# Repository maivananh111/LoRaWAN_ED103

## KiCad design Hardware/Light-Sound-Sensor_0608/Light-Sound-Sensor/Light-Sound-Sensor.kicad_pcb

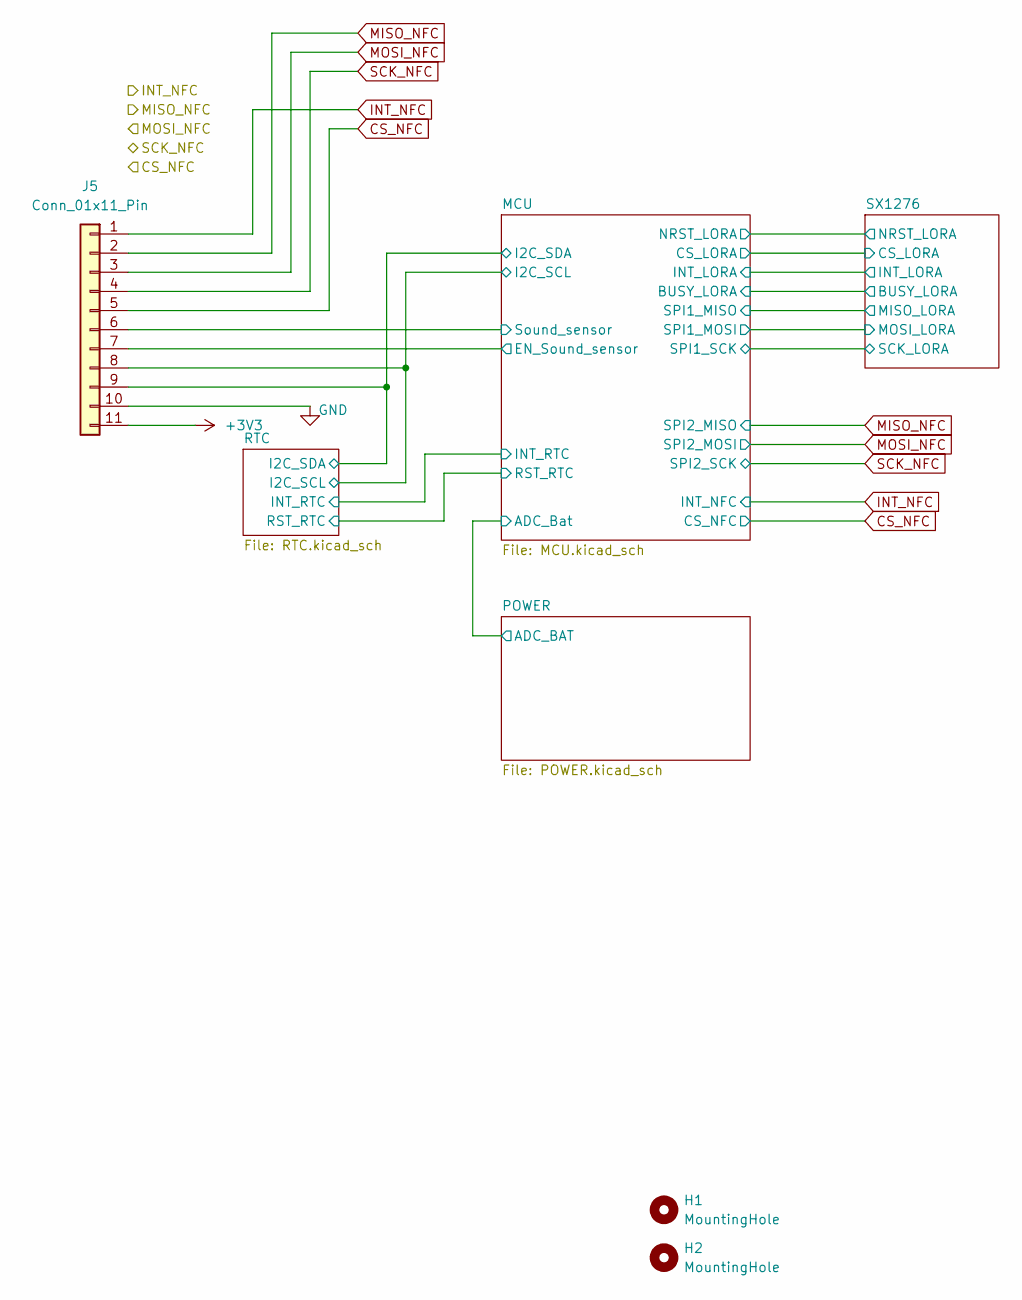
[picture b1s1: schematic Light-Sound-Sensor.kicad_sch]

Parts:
H1, H2: MountingHole; MountingHole_3.2mm_M3_DIN965_Pad
J5: Conn_01x11_Pin; PinHeader_1x11_P2.54mm_Vertical; JLC C5116357

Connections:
+3V3: J5.11; also elsewhere on the board
/MCU/EN_Sound_sensor: J5.7; also elsewhere on the board
/MCU/I2C_SCL: J5.8; also elsewhere on the board
/MCU/I2C_SDA: J5.9; also elsewhere on the board
/MCU/Sound_sensor: J5.6; also elsewhere on the board
CS_NFC: J5.5; also elsewhere on the board
GND: J5.10; also elsewhere on the board
INT_NFC: J5.1; also elsewhere on the board
MISO_NFC: J5.2; also elsewhere on the board
MOSI_NFC: J5.3; also elsewhere on the board
SCK_NFC: J5.4; also elsewhere on the board

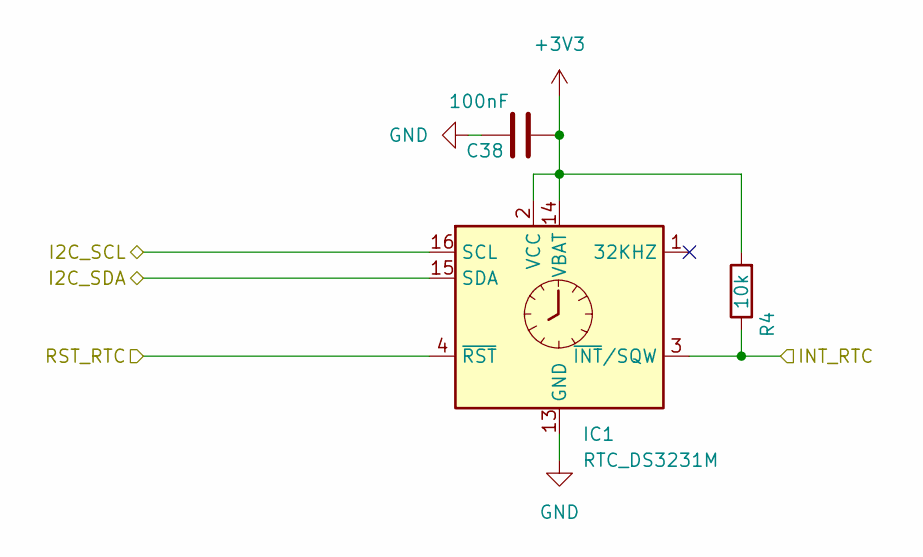
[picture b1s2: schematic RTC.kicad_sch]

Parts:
C38: 100nF; C_0603_1608Metric; JLC C14663
IC1: RTC_DS3231M; SOIC-16W_7.5x10.3mm_P1.27mm; JLC C9866
R4: 10k; R_0603_1608Metric; JLC C25804

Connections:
+3V3: C38.2, IC1.2 (VCC), IC1.14 (VBAT), R4.2; also elsewhere on the board
/MCU/I2C_SCL: IC1.16 (SCL); also elsewhere on the board
/MCU/I2C_SDA: IC1.15 (SDA); also elsewhere on the board
/MCU/INT_RTC: IC1.3 (~INT/SQW), R4.1; also elsewhere on the board
/MCU/RST_RTC: IC1.4 (~RST); also elsewhere on the board
GND: C38.1, IC1.5 (GND), IC1.6 (GND), IC1.7 (GND), IC1.8 (GND), IC1.9 (GND), IC1.10 (GND), IC1.11 (GND), IC1.12 (GND), IC1.13 (GND); also elsewhere on the board

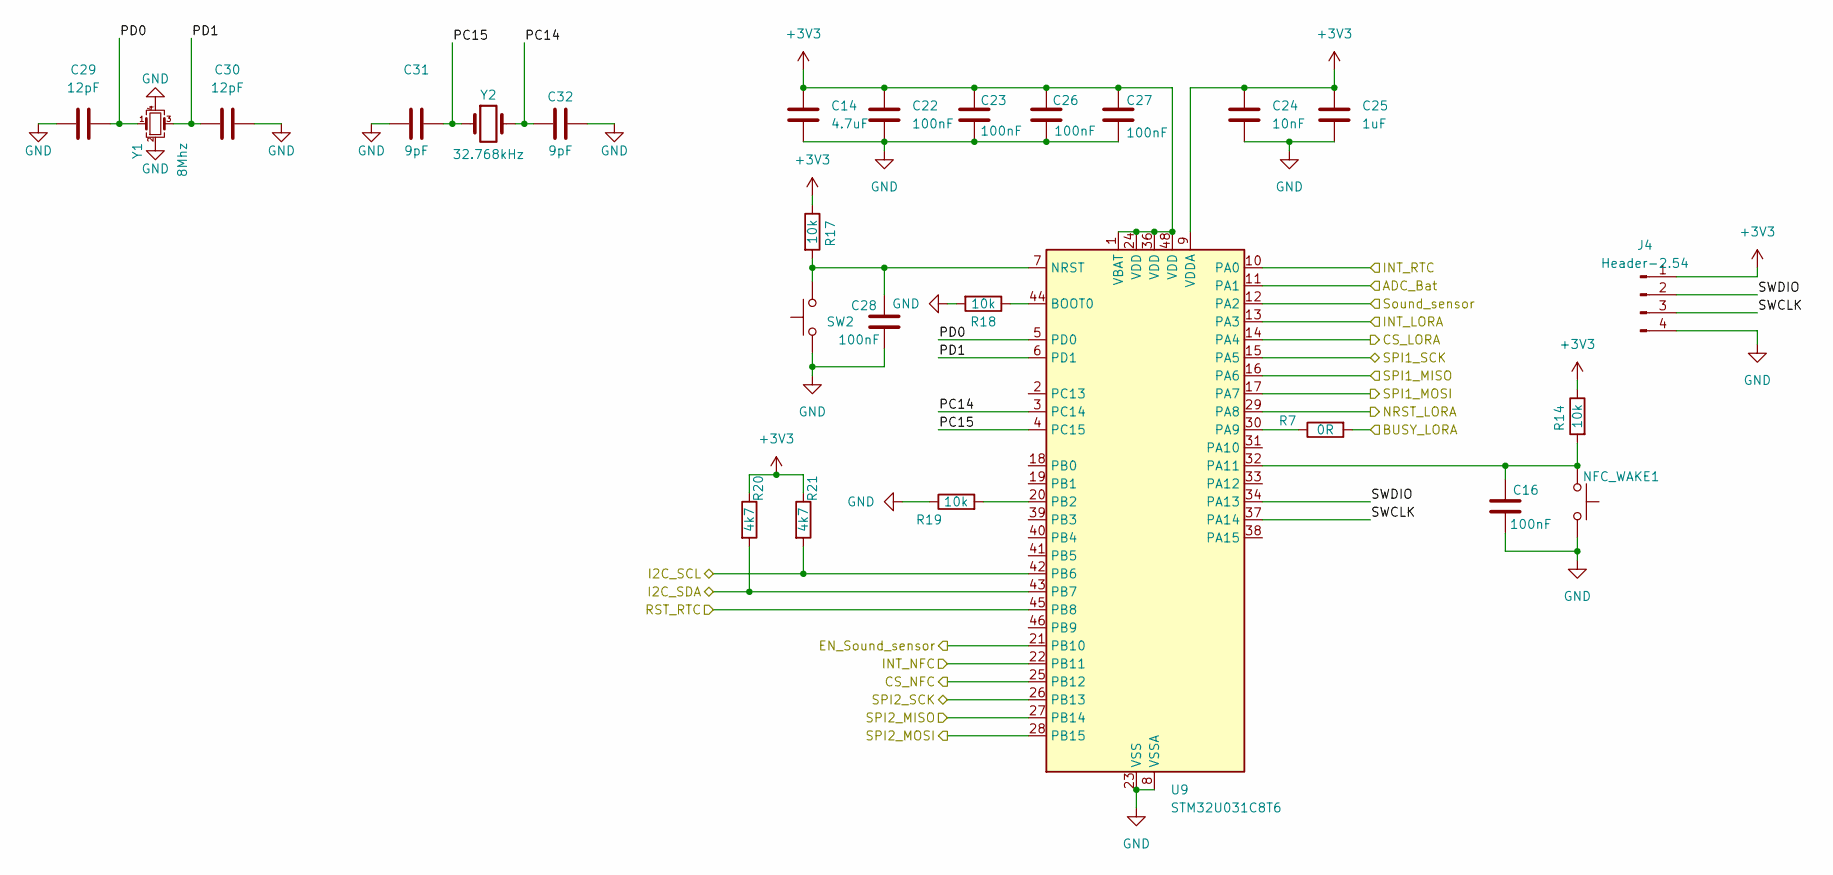
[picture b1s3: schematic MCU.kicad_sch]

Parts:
C14: 4.7uF; C_0603_1608Metric; JLC C76615
C16, C22, C23, C26, C27, C28: 100nF; C_0603_1608Metric; JLC C14663
C24: 10nF; C_0603_1608Metric; JLC C43253
C25: 1uF; C_0603_1608Metric; JLC C126631
C29, C30: 12pF; C_0603_1608Metric; JLC C1642
C31, C32: 9pF; C_0603_1608Metric; JLC C513579
J4: Header-2.54; PinHeader_1x04_P2.54mm_Vertical
NFC_WAKE1: SW_Tactile; SW_SPST_PTS810; JLC C221896
R7: 0R; R_0603_1608Metric; JLC C21189
R14, R17, R18, R19: 10k; R_0603_1608Metric; JLC C25804
R20, R21: 4k7; R_0603_1608Metric; JLC C23162
SW2: SW_Tactile; SW_SPST_PTS810; JLC C221896
U9: STM32U031C8T6; LQFP-48_7x7mm_P0.5mm
Y1: 8Mhz; Crystal_SMD_3225-4Pin_3.2x2.5mm; part C2857622; JLC C400090
Y2: 32.768kHz; Crystal_SMD_3215-2Pin_3.2x1.5mm; Part C2848222; JLC C620155

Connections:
+3V3: C14.1, C22.2, C23.1, C24.1, C25.1, C26.1, C27.1, J4.1, R14.1, R17.1, R20.1, R21.1, U9.1 (VBAT), U9.9 (VDDA), U9.24 (VDD), U9.36 (VDD), U9.48 (VDD); also elsewhere on the board
/MCU/ADC_Bat: U9.11 (PA1); also elsewhere on the board
/MCU/BUSY_LORA: R7.2; also elsewhere on the board
/MCU/CS_LORA: U9.14 (PA4); also elsewhere on the board
/MCU/EN_Sound_sensor: U9.21 (PB10); also elsewhere on the board
/MCU/I2C_SCL: R21.2, U9.42 (PB6); also elsewhere on the board
/MCU/I2C_SDA: R20.2, U9.43 (PB7); also elsewhere on the board
/MCU/INT_LORA: U9.13 (PA3); also elsewhere on the board
/MCU/INT_RTC: U9.10 (PA0); also elsewhere on the board
/MCU/NRST_LORA: U9.29 (PA8); also elsewhere on the board
/MCU/PC14: C32.1, U9.3 (PC14), Y2.2
/MCU/PC15: C31.2, U9.4 (PC15), Y2.1
/MCU/PD0: C29.2, U9.5 (PD0), Y1.1
/MCU/PD1: C30.1, U9.6 (PD1), Y1.3
/MCU/RST_RTC: U9.45 (PB8); also elsewhere on the board
/MCU/SPI1_MISO: U9.16 (PA6); also elsewhere on the board
/MCU/SPI1_MOSI: U9.17 (PA7); also elsewhere on the board
/MCU/SPI1_SCK: U9.15 (PA5); also elsewhere on the board
/MCU/SWCLK: J4.3, U9.37 (PA14)
/MCU/SWDIO: J4.2, U9.34 (PA13)
/MCU/Sound_sensor: U9.12 (PA2); also elsewhere on the board
CS_NFC: U9.25 (PB12); also elsewhere on the board
GND: C14.2, C16.1, C22.1, C23.2, C24.2, C25.2, C26.2, C27.2, C28.1, C29.1, C30.2, C31.1, C32.2, J4.4, NFC_WAKE1.1, R18.2, R19.1, SW2.1, U9.8 (VSSA), U9.23 (VSS), U9.35 (VSS), U9.47 (VSS), Y1.2, Y1.4; also elsewhere on the board
INT_NFC: U9.22 (PB11); also elsewhere on the board
MISO_NFC: U9.27 (PB14); also elsewhere on the board
MOSI_NFC: U9.28 (PB15); also elsewhere on the board
unnamed: R18.1, U9.44 (BOOT0)
unnamed: C28.2, R17.2, SW2.2, U9.7 (NRST)
unnamed: R7.1, U9.30 (PA9)
unnamed: C16.2, NFC_WAKE1.2, R14.2, U9.32 (PA11)
unnamed: R19.2, U9.20 (PB2)
SCK_NFC: U9.26 (PB13); also elsewhere on the board

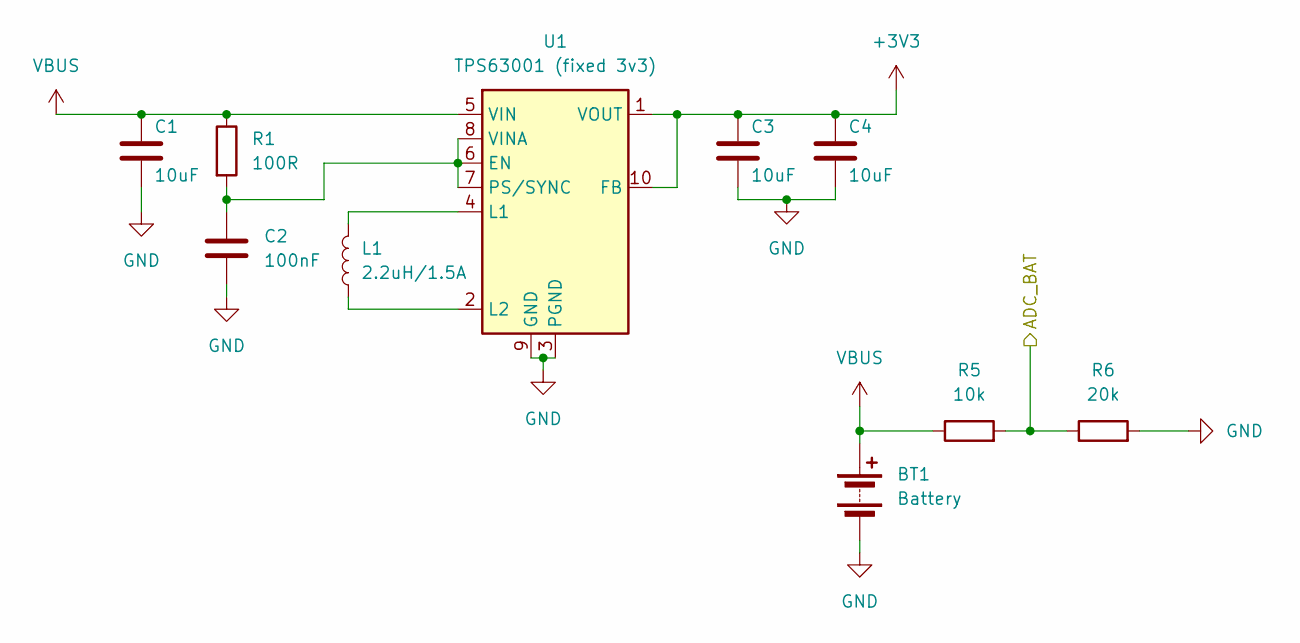
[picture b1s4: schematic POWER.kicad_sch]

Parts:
BT1: Battery; BAT_BC3AAPC
C1: 10uF; C_0603_1608Metric; JLC C91150
C2: 100nF; C_0603_1608Metric; JLC C116838
C3, C4: 10uF; C_0603_1608Metric; JLC C96446
L1: 2.2uH/1.5A; L_0806; Part C439304; JLC C439304
R1: 100R; R_0603_1608Metric; JLC C5123580
R5: 10k; R_0603_1608Metric; JLC C25804
R6: 20k; R_0603_1608Metric; JLC C4184
U1: TPS63001 (fixed 3v3); Texas_DRC0010J_ThermalVias; JLC C28060

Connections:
+3V3: C3.1, C4.1, U1.1 (VOUT), U1.10 (FB); also elsewhere on the board
/MCU/ADC_Bat: R5.2, R6.1; also elsewhere on the board
GND: BT1.2 (-), C1.2, C2.2, C3.2, C4.2, R6.2, U1.3 (PGND), U1.9 (GND), U1.11 (PGND); also elsewhere on the board
unnamed: C2.1, R1.2, U1.6 (EN), U1.7 (PS/SYNC), U1.8 (VINA)
unnamed: L1.2, U1.4 (L1)
unnamed: L1.1, U1.2 (L2)
VBUS: BT1.1 (+), C1.1, R1.1, R5.1, U1.5 (VIN)

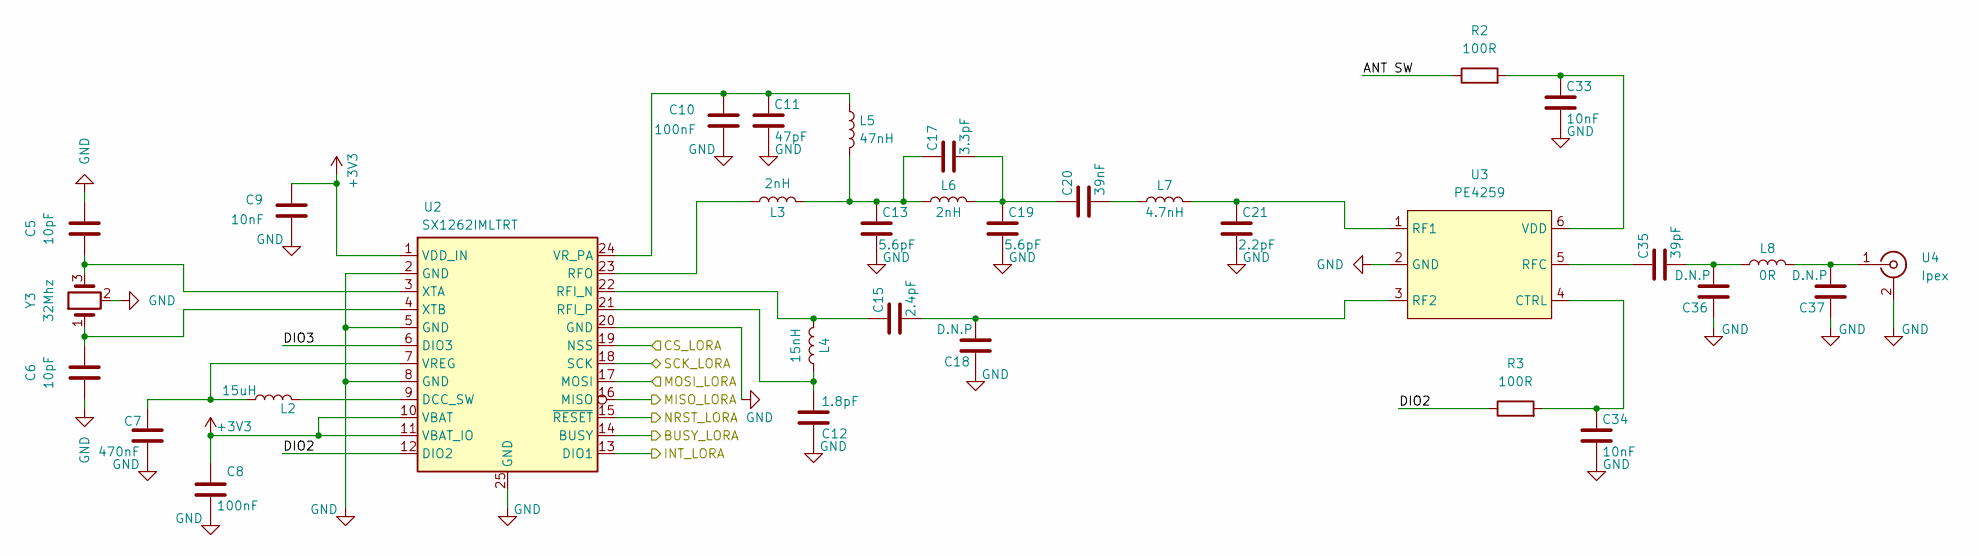
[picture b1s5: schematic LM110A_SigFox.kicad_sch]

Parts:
C5, C6: 10pF; C_0603_1608Metric; JLC C1634
C7: 470nF; C_0603_1608Metric; JLC C77572
C8, C10: 100nF; C_0603_1608Metric; JLC C14663
C9, C33, C34: 10nF; C_0603_1608Metric; JLC C43253
C11: 47pF; C_0603_1608Metric; JLC C105622
C12: 1.8pF; C_0603_1608Metric; JLC C1640
C13, C19: 5.6pF; C_0603_1608Metric; JLC C1674
C15: 2.4pF; C_0603_1608Metric; JLC C27741
C17: 3.3pF; C_0603_1608Metric; JLC C1660
C18, C36, C37: D.N.P; C_0603_1608Metric
C20: 39nF; C_0603_1608Metric; JLC C107091
C21: 2.2pF; C_0603_1608Metric; JLC C1651
C35: 39pF; C_0603_1608Metric; JLC C107049
L2: 15uH; L_0603_1608Metric; JLC C57838
L3, L6: 2nH; L_0603_1608Metric; JLC C370234
L4: 15nH; L_0603_1608Metric; JLC C23651
L5: 47nH; L_0603_1608Metric; JLC C29683
L7: 4.7nH; L_0603_1608Metric; JLC C1030
L8: 0R; L_0603_1608Metric; JLC C21189
R2, R3: 100R; R_0603_1608Metric; JLC C22775
U2: SX1262IMLTRT; QFN-24-1EP_4x4mm_P0.5mm_EP2.6x2.6mm
U3: PE4259; SOT-363_SC-70-6; JLC C470892
U4: Ipex; Conn_IPEX_ANT; JLC C496552
Y3: 32Mhz; Crystal_SMD_3225-4Pin_3.2x2.5mm; JLC C9009

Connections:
+3V3: C8.1, C9.1, U2.1 (VDD_IN), U2.10 (VBAT), U2.11 (VBAT_IO); also elsewhere on the board
/MCU/BUSY_LORA: U2.14 (BUSY); also elsewhere on the board
/MCU/CS_LORA: U2.19 (NSS); also elsewhere on the board
/MCU/INT_LORA: U2.13 (DIO1); also elsewhere on the board
/MCU/NRST_LORA: U2.15 (~RESET); also elsewhere on the board
/MCU/SPI1_MISO: U2.16 (MISO); also elsewhere on the board
/MCU/SPI1_MOSI: U2.17 (MOSI); also elsewhere on the board
/MCU/SPI1_SCK: U2.18 (SCK); also elsewhere on the board
/SX1276/ANT SW: R2.1
/SX1276/DIO2: R3.1, U2.12 (DIO2)
/SX1276/DIO3: U2.6 (DIO3)
GND: C5.2, C6.1, C7.2, C8.2, C9.2, C10.2, C11.2, C12.1, C13.2, C18.1, C19.2, C21.2, C33.2, C34.2, C36.1, C37.1, U2.2 (GND), U2.5 (GND), U2.8 (GND), U2.20 (GND), U2.25 (GND), U3.2 (GND), U4.2, U4.3, Y3.2, Y3.4; also elsewhere on the board
unnamed: C13.1, C17.1, L3.2, L5.2, L6.1
unnamed: C17.2, C19.1, C20.1, L6.2
unnamed: C20.2, L7.1
unnamed: C35.2, C36.2, L8.1
unnamed: C37.2, L8.2, U4.1
unnamed: L2.2, U2.9 (DCC_SW)
unnamed: C15.1, L4.2, U2.22 (RFI_N)
unnamed: C12.2, L4.1, U2.21 (RFI_P)
unnamed: L3.1, U2.23 (RFO)
unnamed: C7.1, L2.1, U2.7 (VREG)
unnamed: C10.1, C11.1, L5.1, U2.24 (VR_PA)
unnamed: C5.1, U2.3 (XTA), Y3.3
unnamed: C6.2, U2.4 (XTB), Y3.1
unnamed: C34.1, R3.2, U3.4 (CTRL)
unnamed: C21.1, L7.2, U3.1 (RF1)
unnamed: C15.2, C18.2, U3.3 (RF2)
unnamed: C35.1, U3.5 (RFC)
unnamed: C33.1, R2.2, U3.6 (VDD)

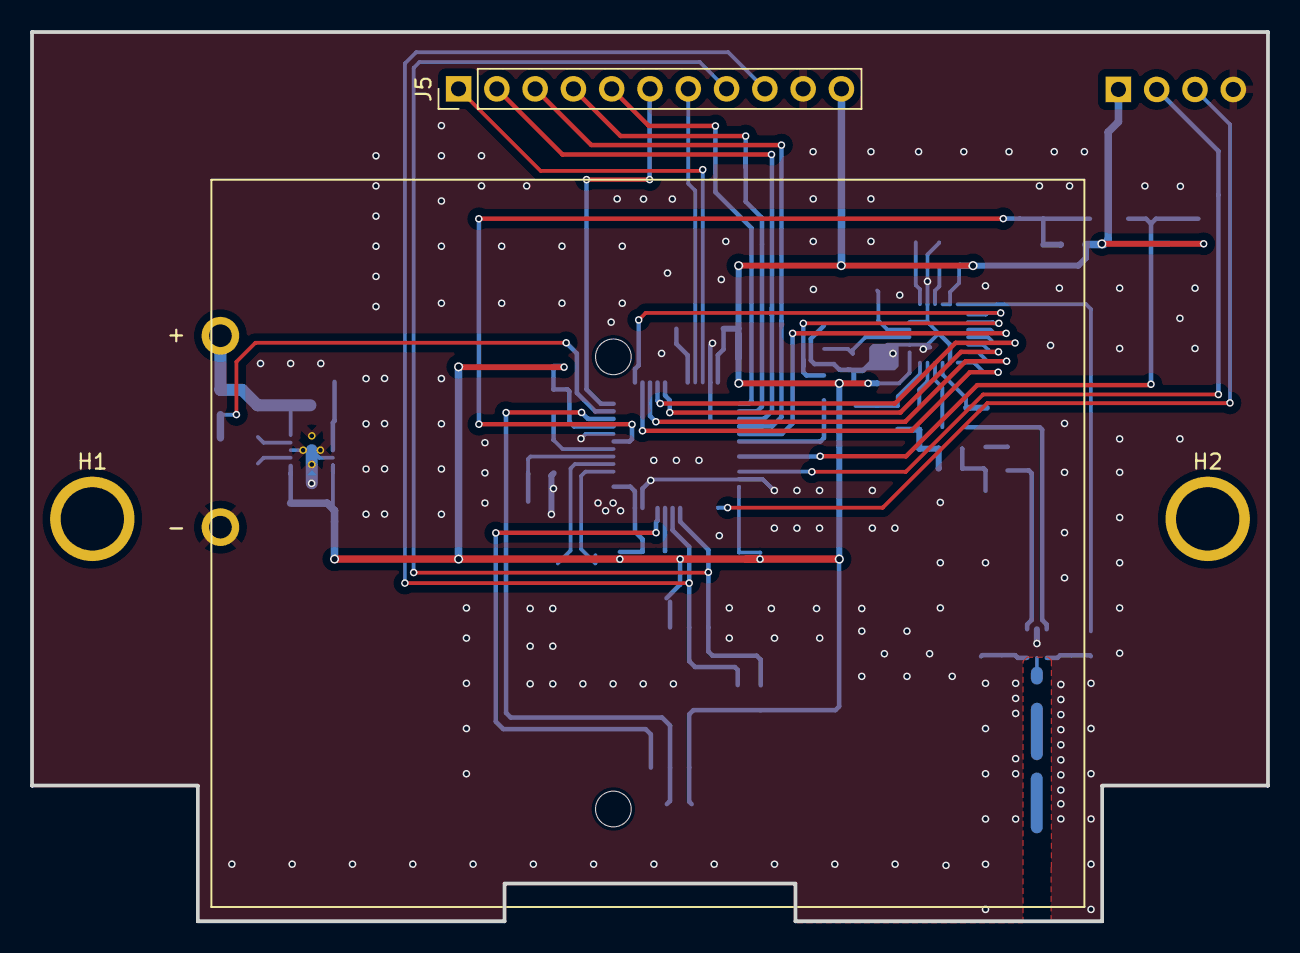
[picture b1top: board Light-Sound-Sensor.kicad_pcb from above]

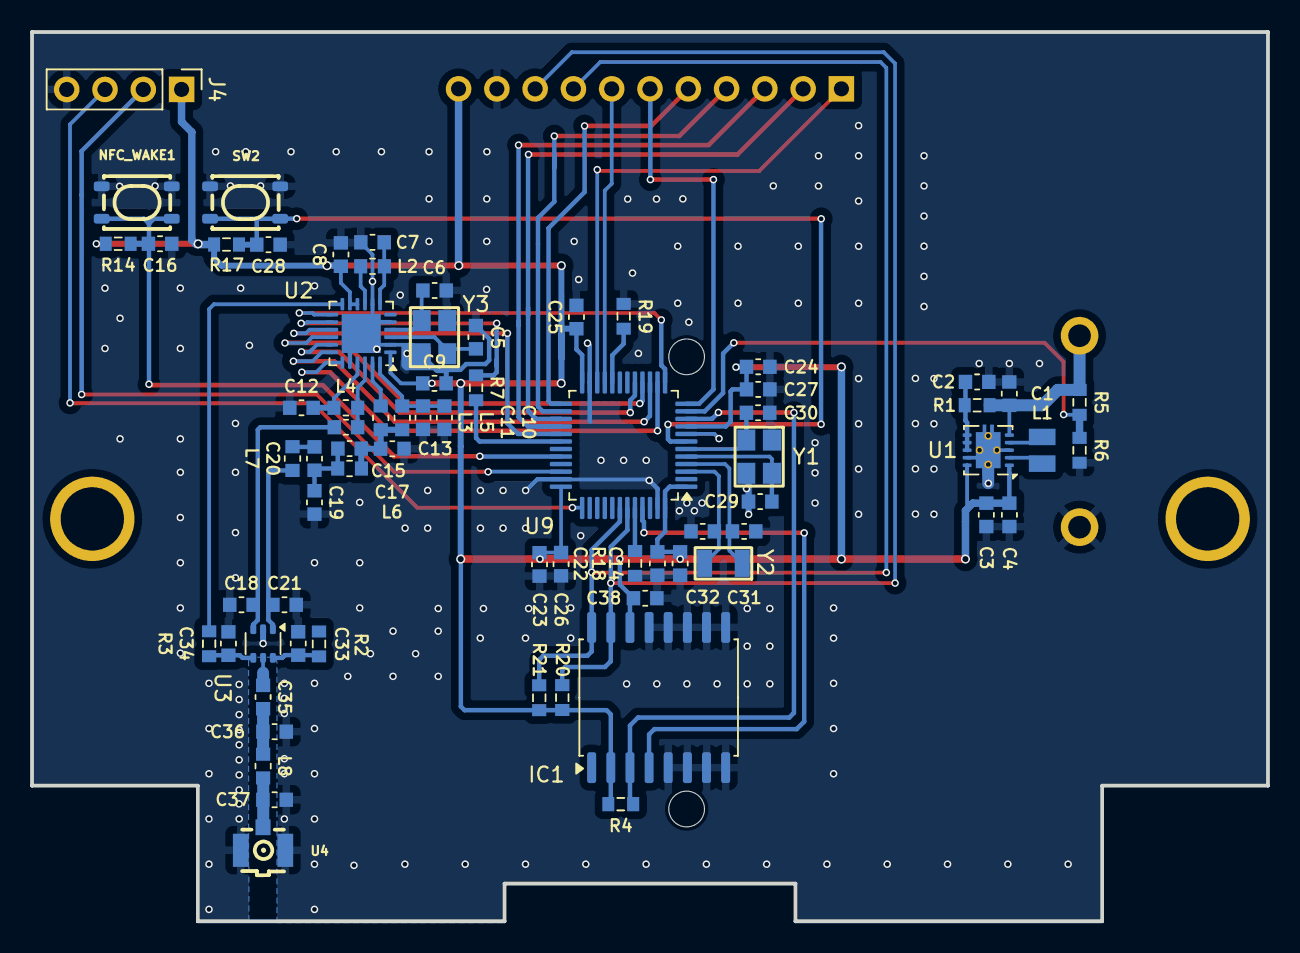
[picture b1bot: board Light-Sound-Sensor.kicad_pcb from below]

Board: 2 copper layers, 82.0 x 59.0 mm, 75 parts (71 on the bottom side), 55 nets.

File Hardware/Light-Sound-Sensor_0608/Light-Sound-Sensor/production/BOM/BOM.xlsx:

Designator | Footprint | Quantity | Value | LCSC Part # | Digikey
BT1 | BAT_BC3AAPC | 1 | Battery |  | BC3AAPC-ND
C1, C3, C4 | 603 | 3 | 10uF | C96446
C10, C16, C2, C22, C23, C26, C27, C28, C38, C8 | 603 | 10 | 100nF | C14663
C11 | 603 | 1 | 47pF | C105622
C12 | 603 | 1 | 1.8pF | C1640
C13, C19 | 603 | 2 | 5.6pF | C1674
C14 | 603 | 1 | 4.7uF | C76615
C15 | 603 | 1 | 2.4pF | C27741
C17 | 603 | 1 | 3.3pF | C1660
C20 | 603 | 1 | 39nF | C107091
C21 | 603 | 1 | 2.2pF | C1651
C24, C33, C34, C9 | 603 | 4 | 10nF | C43253
C25 | 603 | 1 | 1uF | C126631
C29, C30 | 603 | 2 | 12pF | C1642
C31, C32 | 603 | 2 | 9pF | C513579
C35 | 603 | 1 | 39pF | C107049
C5, C6 | 603 | 2 | 10pF | C1634
C7 | 603 | 1 | 470nF | C77572
IC1 | SOIC-16W_7.5x10.3mm_P1.27mm | 1 | RTC_DS3231M | NPN
J5 | PinHeader_1x11_P2.54mm_Vertical | 1 | Conn_01x11_Pin | C5116357
L1 | L_0806 | 1 | 2.2uH/1.5A | C439304
L2 | 603 | 1 | 15uH | C57838
L3, L6 | 603 | 2 | 2nH | C370234
L4 | 603 | 1 | 15nH | C23651
L5 | 603 | 1 | 47nH | C29683
L7 | 603 | 1 | 4.7nH | C1030
L8, R7 | 603 | 2 | 0R | C21189
NFC_WAKE1, SW2 | SW_SPST_PTS810 | 2 | SW_Tactile | C221896
R1, R2, R3 | 603 | 3 | 100R | C22775
R14, R17, R18, R19, R4, R5 | 603 | 6 | 10k | C25804
R20, R21 | 603 | 2 | 4k7 | C23162
R6 | 603 | 1 | 20k | C4184
U1 | Texas_DRC0010J_ThermalVias | 1 | TPS63001 (fixed 3v3) | C28060
U2 | QFN-24-1EP_4x4mm_P0.5mm_EP2.6x2.6mm | 1 | SX1262IMLTRT | C191341
U3 | SOT-363_SC-70-6 | 1 | PE4259 | C470892
U4 | Conn_IPEX_ANT | 1 | Ipex | C496552
U9 | LQFP-48_7x7mm_P0.5mm | 1 | STM32U031C8T6 |  | 497-STM32U031C8T6-ND
Y1 | Crystal_SMD_3225-4Pin_3.2x2.5mm | 1 | 8Mhz | C400090
Y2 | Crystal_SMD_3215-2Pin_3.2x1.5mm | 1 | 32.768kHz | C620155
Y3 | Crystal_SMD_3225-4Pin_3.2x2.5mm | 1 | 32Mhz | C9009

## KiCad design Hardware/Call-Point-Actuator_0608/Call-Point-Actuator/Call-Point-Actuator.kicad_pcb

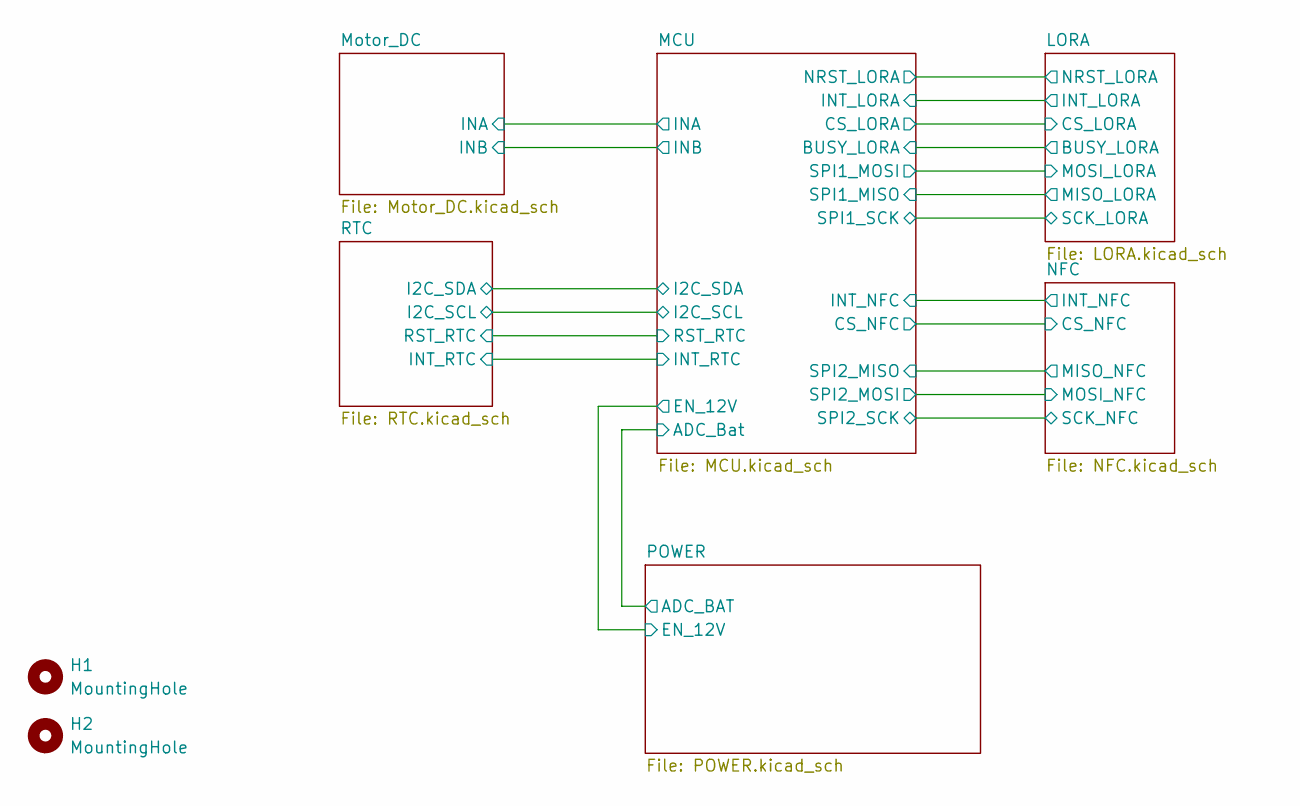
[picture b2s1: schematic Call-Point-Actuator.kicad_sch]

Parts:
H1, H2: MountingHole; MountingHole_3.2mm_M3_DIN965_Pad

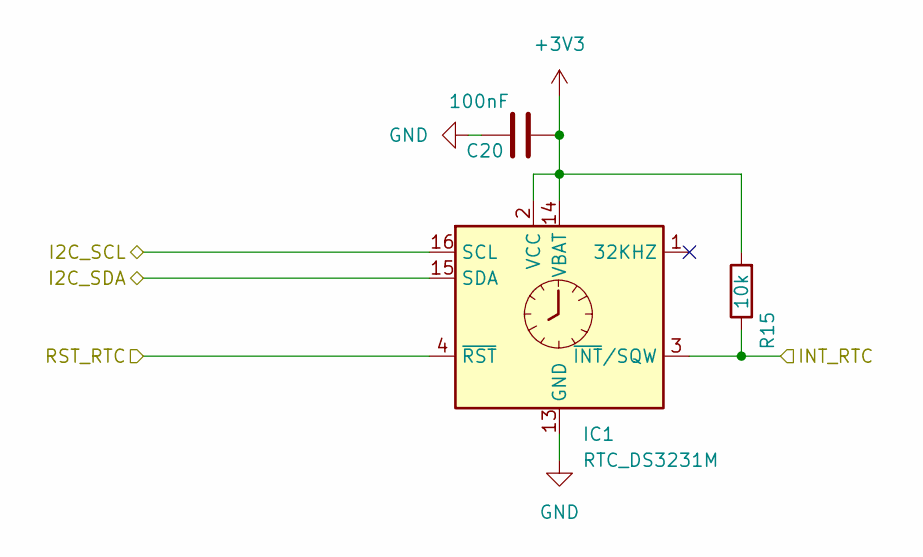
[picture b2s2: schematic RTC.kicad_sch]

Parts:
C20: 100nF; C_0603_1608Metric; JLC C14663
IC1: RTC_DS3231M; SOIC-16W_7.5x10.3mm_P1.27mm; JLC C9866
R15: 10k; R_0603_1608Metric; JLC C25804

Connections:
+3V3: C20.2, IC1.2 (VCC), IC1.14 (VBAT), R15.2; also elsewhere on the board
/MCU/I2C_SCL: IC1.16 (SCL); also elsewhere on the board
/MCU/I2C_SDA: IC1.15 (SDA); also elsewhere on the board
/MCU/INT_RTC: IC1.3 (~INT/SQW), R15.1; also elsewhere on the board
/MCU/RST_RTC: IC1.4 (~RST); also elsewhere on the board
GND: C20.1, IC1.5 (GND), IC1.6 (GND), IC1.7 (GND), IC1.8 (GND), IC1.9 (GND), IC1.10 (GND), IC1.11 (GND), IC1.12 (GND), IC1.13 (GND); also elsewhere on the board

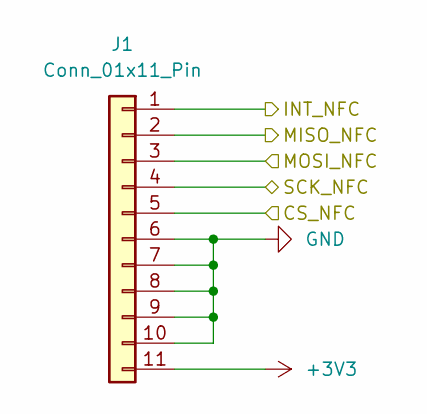
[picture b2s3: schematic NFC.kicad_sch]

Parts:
J1: Conn_01x11_Pin; PinHeader_1x11_P2.54mm_Vertical; JLC C5116357

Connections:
+3V3: J1.11; also elsewhere on the board
/MCU/CS_NFC: J1.5; also elsewhere on the board
/MCU/INT_NFC: J1.1; also elsewhere on the board
/MCU/SPI2_MISO: J1.2; also elsewhere on the board
/MCU/SPI2_MOSI: J1.3; also elsewhere on the board
/MCU/SPI2_SCK: J1.4; also elsewhere on the board
GND: J1.6, J1.7, J1.8, J1.9, J1.10; also elsewhere on the board

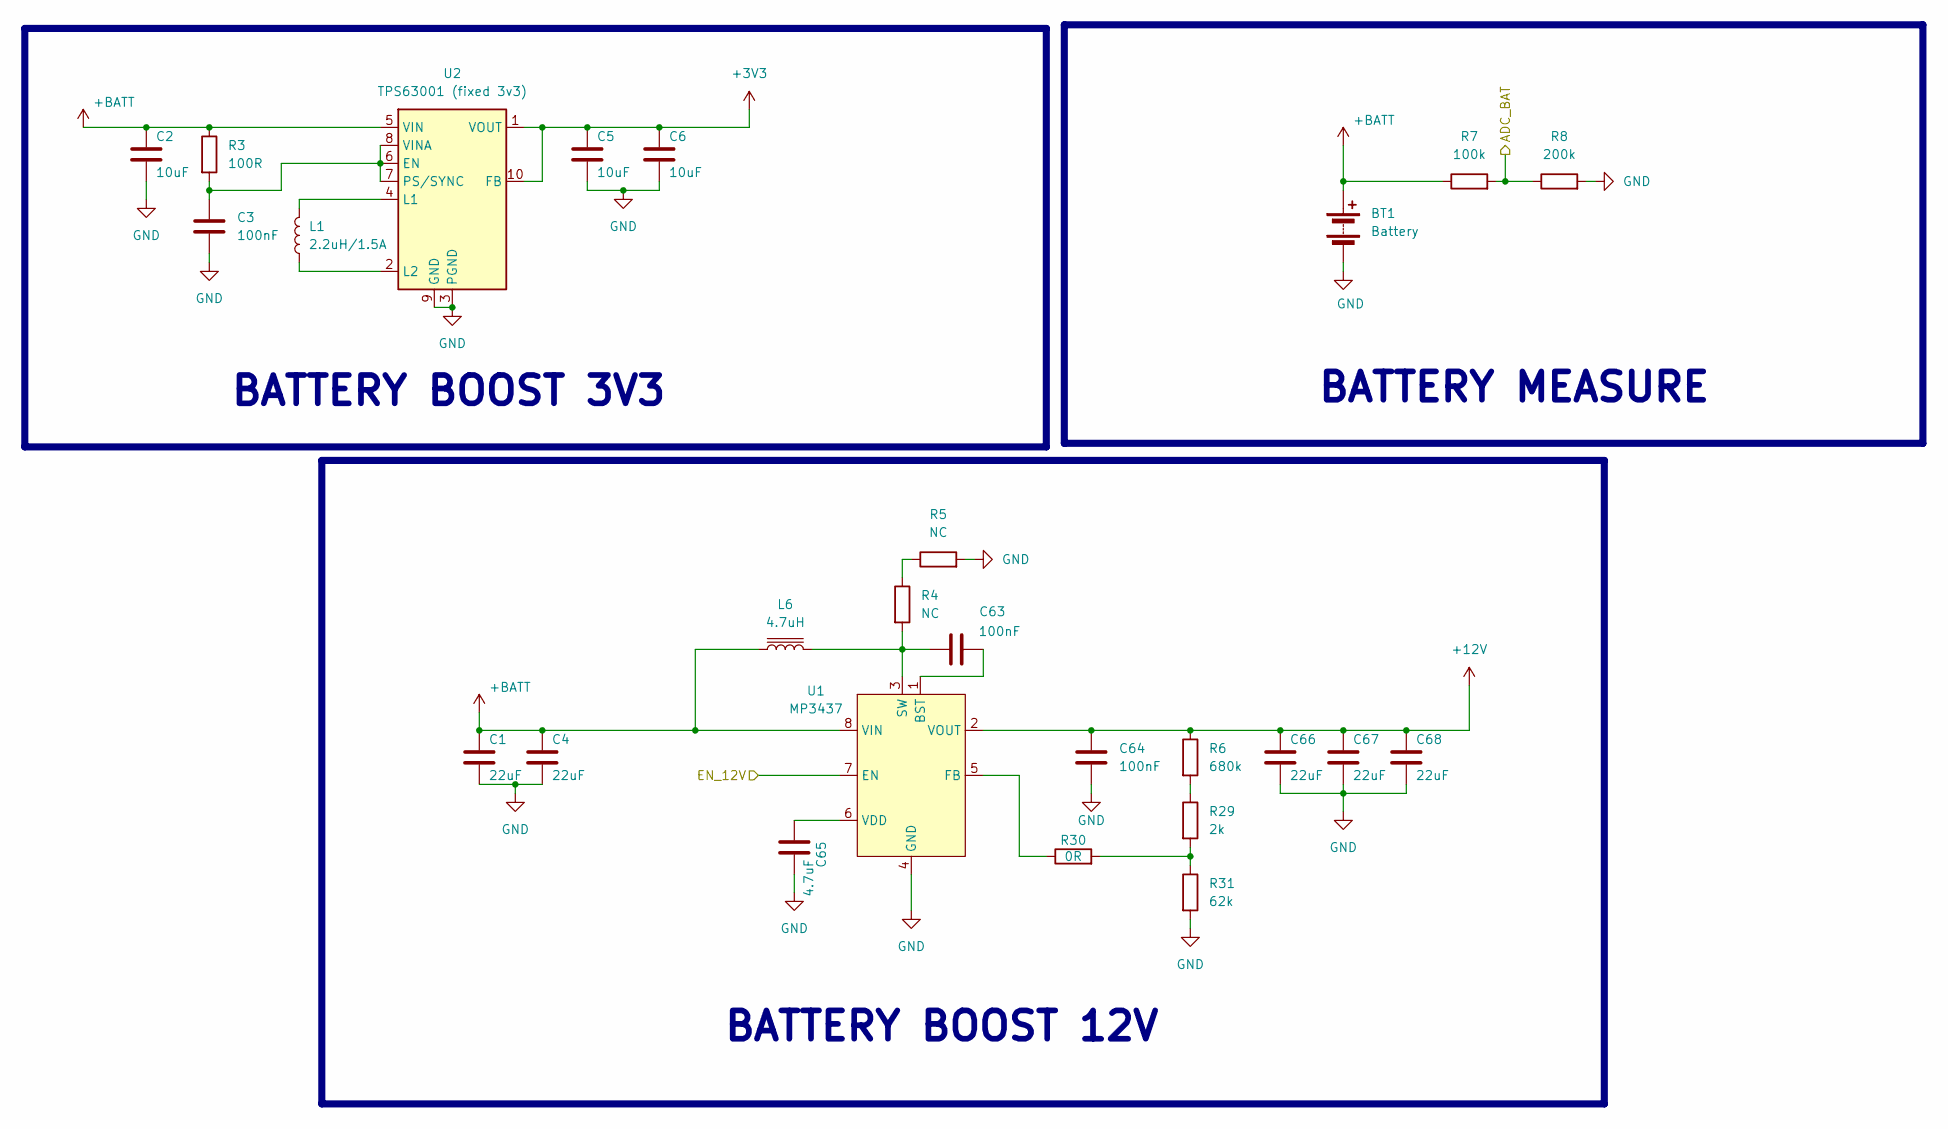
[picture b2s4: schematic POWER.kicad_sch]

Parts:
BT1: Battery; BAT_BC3AAPC
C1, C4, C66, C67, C68: 22uF; C_0603_1608Metric; JLC C84419
C2, C5, C6: 10uF; C_0603_1608Metric; JLC C91150
C3, C63, C64: 100nF; C_0603_1608Metric; JLC C116838
C65: 4.7uF; C_0603_1608Metric; JLC C76615
L1: 2.2uH/1.5A; inductor_0806; Part C439304
L6: 4.7uH; L_4040; JLC C167874
R3: 100R; L_0603_1608Metric; JLC C5123580
R4, R5: NC; L_0603_1608Metric
R6: 680k; L_0603_1608Metric; JLC C25822
R7: 100k; L_0603_1608Metric; JLC C667147
R8: 200k; L_0603_1608Metric; JLC C335089
R29: 2k; L_0603_1608Metric; JLC C72817
R30: 0R; R_0603; JLC C304185
R31: 62k; L_0603_1608Metric; JLC C432812
U1: MP3437; TSOT-23-8
U2: TPS63001 (fixed 3v3); Texas_DRC0010J_ThermalVias; JLC C28060

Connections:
+3V3: C5.1, C6.1, U2.1 (VOUT), U2.10 (FB); also elsewhere on the board
+12V: C64.2, C66.1, C67.1, C68.1, R6.1, U1.2 (VOUT); also elsewhere on the board
+BATT: BT1.1 (+), C1.1, C2.1, C4.1, L6.1, R3.1, R7.1, U1.8 (VIN), U2.5 (VIN)
/MCU/ADC_Bat: R7.2, R8.1; also elsewhere on the board
/MCU/EN_12V: U1.7 (EN); also elsewhere on the board
GND: BT1.2 (-), C1.2, C2.2, C3.2, C4.2, C5.2, C6.2, C64.1, C65.2, C66.2, C67.2, C68.2, R5.2, R8.2, R31.2, U1.4 (GND), U2.3 (PGND), U2.9 (GND), U2.11 (PGND); also elsewhere on the board
unnamed: R4.1, R5.1
unnamed: R6.2, R29.1
unnamed: R29.2, R30.2, R31.1
unnamed: C63.2, U1.1 (BST)
unnamed: R30.1, U1.5 (FB)
unnamed: C63.1, L6.2, R4.2, U1.3 (SW)
unnamed: C65.1, U1.6 (VDD)
unnamed: C3.1, R3.2, U2.6 (EN), U2.7 (PS/SYNC), U2.8 (VINA)
unnamed: L1.2, U2.4 (L1)
unnamed: L1.1, U2.2 (L2)

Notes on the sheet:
BATTERY BOOST 3V3
BATTERY BOOST 12V
BATTERY MEASURE

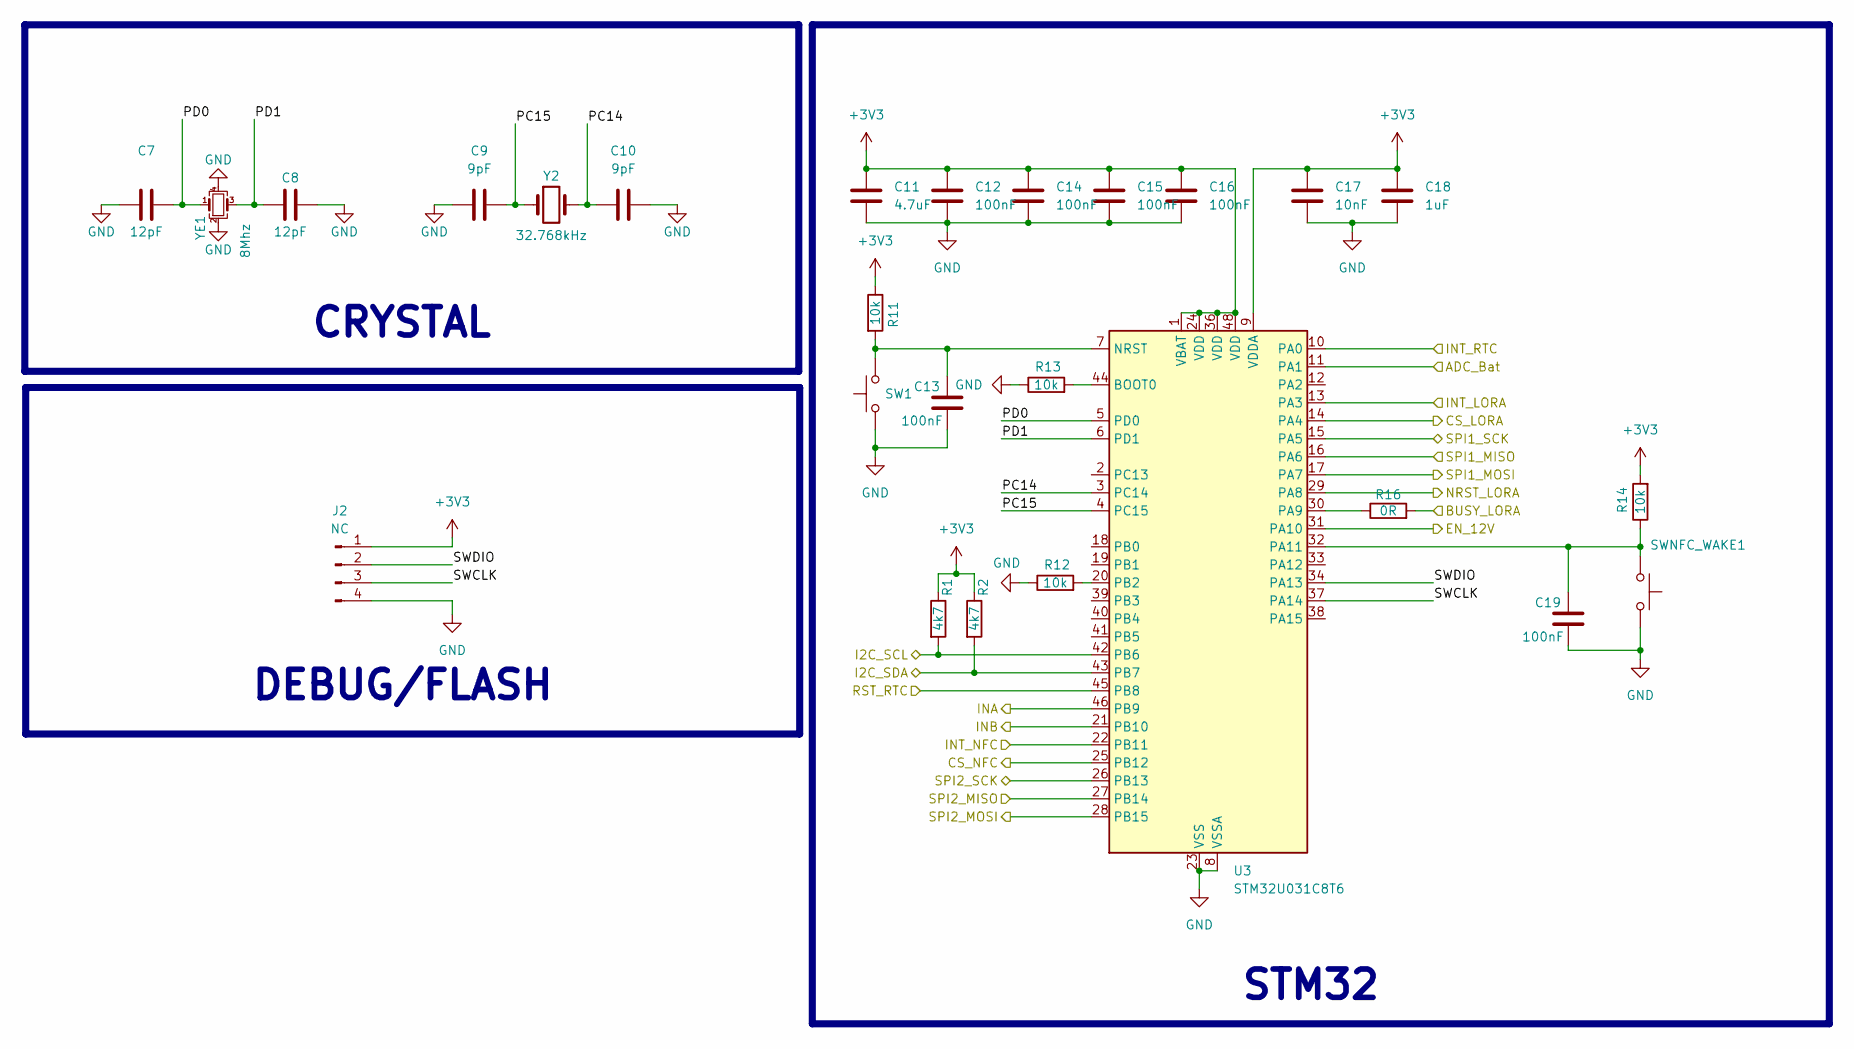
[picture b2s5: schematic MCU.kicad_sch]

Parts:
C7, C8: 12pF; C_0603_1608Metric; JLC C1642
C9, C10: 9pF; C_0603_1608Metric; JLC C513579
C11: 4.7uF; C_0603_1608Metric; JLC C76615
C12, C13, C14, C15, C16, C19: 100nF; C_0603_1608Metric; JLC C14663
C17: 10nF; C_0603_1608Metric; JLC C43253
C18: 1uF; C_0603_1608Metric; JLC C126631
J2: NC; PinHeader_1x04_P2.54mm_Vertical
R1, R2: 4k7; R_0603_1608Metric; JLC C23162
R11, R12, R13, R14: 10k; R_0603_1608Metric; JLC C25804
R16: 0R; R_0603_1608Metric; JLC C304185
SW1: SW_Tactile; SW_SPST_PTS810; JLC C221896
SWNFC_WAKE1: SW_Tactile; SW_SPST_PTS810; JLC C221896
U3: STM32U031C8T6; LQFP-48_7x7mm_P0.5mm
Y2: 32.768kHz; Crystal_SMD_3215-2Pin_3.2x1.5mm; JLC C620155
YE1: 8Mhz; Crystal_SMD_3225-4Pin_3.2x2.5mm; JLC C400090

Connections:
+3V3: C11.1, C12.2, C14.2, C15.2, C16.2, C17.2, C18.2, J2.1, R1.1, R2.1, R11.1, R14.2, U3.1 (VBAT), U3.9 (VDDA), U3.24 (VDD), U3.36 (VDD), U3.48 (VDD); also elsewhere on the board
/LORA/BUSY_LORA: R16.2; also elsewhere on the board
/LORA/CS_LORA: U3.14 (PA4); also elsewhere on the board
/LORA/INT_LORA: U3.13 (PA3); also elsewhere on the board
/LORA/MISO_LORA: U3.16 (PA6); also elsewhere on the board
/LORA/MOSI_LORA: U3.17 (PA7); also elsewhere on the board
/LORA/NRST_LORA: U3.29 (PA8); also elsewhere on the board
/LORA/SCK_LORA: U3.15 (PA5); also elsewhere on the board
/MCU/ADC_Bat: U3.11 (PA1); also elsewhere on the board
/MCU/CS_NFC: U3.25 (PB12); also elsewhere on the board
/MCU/EN_12V: U3.31 (PA10); also elsewhere on the board
/MCU/I2C_SCL: R1.2, U3.42 (PB6); also elsewhere on the board
/MCU/I2C_SDA: R2.2, U3.43 (PB7); also elsewhere on the board
/MCU/INA: U3.46 (PB9); also elsewhere on the board
/MCU/INB: U3.21 (PB10); also elsewhere on the board
/MCU/INT_NFC: U3.22 (PB11); also elsewhere on the board
/MCU/INT_RTC: U3.10 (PA0); also elsewhere on the board
/MCU/PC14: C10.1, U3.3 (PC14), Y2.2
/MCU/PC15: C9.2, U3.4 (PC15), Y2.1
/MCU/PD0: C7.2, U3.5 (PD0), YE1.1
/MCU/PD1: C8.1, U3.6 (PD1), YE1.3
/MCU/RST_RTC: U3.45 (PB8); also elsewhere on the board
/MCU/SPI2_MISO: U3.27 (PB14); also elsewhere on the board
/MCU/SPI2_MOSI: U3.28 (PB15); also elsewhere on the board
/MCU/SPI2_SCK: U3.26 (PB13); also elsewhere on the board
/MCU/SWCLK: J2.3, U3.37 (PA14)
/MCU/SWDIO: J2.2, U3.34 (PA13)
GND: C7.1, C8.2, C9.1, C10.2, C11.2, C12.1, C13.1, C14.1, C15.1, C16.1, C17.1, C18.1, C19.1, J2.4, R12.1, R13.1, SW1.1, SWNFC_WAKE1.1, U3.8 (VSSA), U3.23 (VSS), U3.35 (VSS), U3.47 (VSS), YE1.2, YE1.4; also elsewhere on the board
unnamed: R13.2, U3.44 (BOOT0)
unnamed: C13.2, R11.2, SW1.2, U3.7 (NRST)
unnamed: R16.1, U3.30 (PA9)
unnamed: C19.2, R14.1, SWNFC_WAKE1.2, U3.32 (PA11)
unnamed: R12.2, U3.20 (PB2)

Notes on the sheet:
DEBUG/FLASH
STM32
CRYSTAL
